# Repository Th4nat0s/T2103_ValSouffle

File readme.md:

Blow Gun controller for CNC
===========================

Print it on your CNC !

Push code to arduino
--------------------------------

### Arduino
Usb connection 
arduino framework 

Tips
----
`./serial` launch serial console through buspirate  
`pio run -t idedata` update libs, perpare env  
`pio run -t fuses` set the fuses  
`pio run -t upload -e release|debug` upload  a specific release version without serial debug  
`pio platform update --dry-run` check for updates

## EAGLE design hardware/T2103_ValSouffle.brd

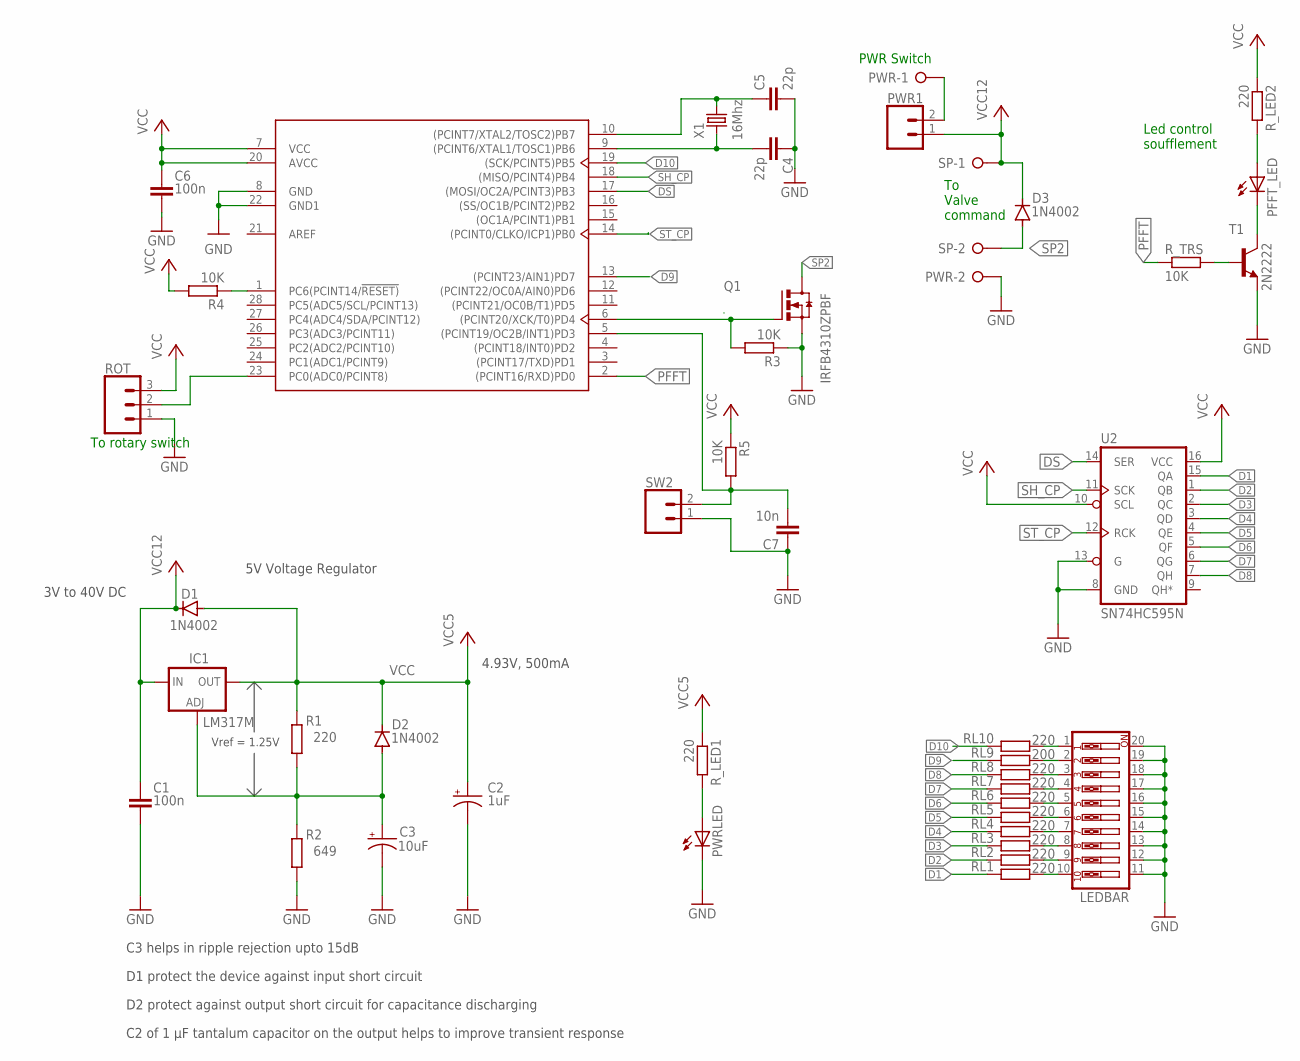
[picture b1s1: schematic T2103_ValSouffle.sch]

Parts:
C1, C6: 100n; C050-030X075
C2: 1uF; E1,8-4
C3: 10uF; E1,8-4
C4, C5: 22p; C025-025X050
C7: 10n; C025-025X050
D1, D2, D3: 1N4002; DO41-10
IC1: LM317MB; TO220L1; PARTNUMBER LM317M
LEDBAR: SW_DIP-10; EDG-10
PFFT_LED: LED5MM
PWR: W237-02P; W237-132
PWR1: CONN_02; 1X02
PWRLED: LED5MM
Q1: IRFB4310ZPBF; TO-220
R1: 220; 0207/10
R2: 649; 0207/10
R3, R4, R5: 10K; 0207/10
RL1, RL2, RL3, RL4, RL5, RL6, RL7, RL8, RL10: 220; 0207/10
RL9: 200; 0207/10
ROT: CONN_03; 1X03
R_LED1, R_LED2: 220; 0207/10
R_TRS: 10K; 0207/10
SP: W237-02P; W237-132
SW2: CONN_02; 1X02
T1: 2N2222; TO92-EBC-OVAL
U1: ATMEGA328P-PU; DIP-28
U2: SN74HC595N; DIP16
X1: 16Mhz; XTAL_HC49

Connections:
D1: RL1.2, U2.15 (QA)
D2: RL2.2, U2.1 (QB)
D3: RL3.2, U2.2 (QC)
D4: RL4.2, U2.3 (QD)
D5: RL5.2, U2.4 (QE)
D6: RL6.2, U2.5 (QF)
D7: RL7.2, U2.6 (QG)
D8: RL8.2, U2.7 (QH)
D9: RL9.2, U1.13 ((PCINT23/AIN1)PD7)
D10: RL10.2, U1.19 ((SCK/PCINT5)PB5)
DS: U1.17 ((MOSI/OC2A/PCINT3)PB3), U2.14 (SER)
GND: C1.2, C2.-, C3.-, C4.1, C5.2, C6.2, C7.1, LEDBAR.11, LEDBAR.12, LEDBAR.13, LEDBAR.14, LEDBAR.15, LEDBAR.16, LEDBAR.17, LEDBAR.18, LEDBAR.19, LEDBAR.20, PWR.2, PWRLED.K (C), Q1.S, R2.1, R3.1, ROT.1, SW2.1, T1.E, U1.8 (GND), U1.22 (GND1), U2.8 (GND), U2.13 (G)
unnamed: C3.+, D2.A, IC1.1 (ADJ), R1.1, R2.2
unnamed: C4.2, U1.9 ((PCINT6/XTAL1/TOSC1)PB6), X1.1
unnamed: C5.1, U1.10 ((PCINT7/XTAL2/TOSC2)PB7), X1.2
unnamed: Q1.G, R3.2, U1.6 ((PCINT20/XCK/T0)PD4)
unnamed: R4.1, U1.1 (PC6(PCINT14/!RESET))
unnamed: LEDBAR.1, RL10.1
unnamed: LEDBAR.2, RL9.1
unnamed: LEDBAR.3, RL8.1
unnamed: LEDBAR.4, RL7.1
unnamed: LEDBAR.5, RL6.1
unnamed: LEDBAR.6, RL5.1
unnamed: LEDBAR.7, RL4.1
unnamed: LEDBAR.8, RL3.1
unnamed: LEDBAR.9, RL2.1
unnamed: LEDBAR.10, RL1.1
unnamed: ROT.2, U1.23 (PC0(ADC0/PCINT8))
unnamed: PFFT_LED.A, R_LED2.2
unnamed: PFFT_LED.K (C), T1.C
unnamed: PWRLED.A, R_LED1.2
unnamed: R_TRS.2, T1.B
unnamed: C7.2, R5.2, SW2.2, U1.5 ((PCINT19/OC2B/INT1)PD3)
PFFT: R_TRS.1, U1.2 ((PCINT16/RXD)PD0)
SH_CP: U1.18 ((MISO/PCINT4)PB4), U2.11 (SCK)
SP2: D3.A, Q1.D, SP.2
ST_CP: U1.14 ((PCINT0/CLKO/ICP1)PB0), U2.12 (RCK)
VCC: C2.+, C6.1, D1.A, D2.C, IC1.2 (OUT), R1.2, R4.2, R5.1, ROT.3, R_LED1.1, R_LED2.1, U1.7 (VCC), U1.20 (AVCC), U2.10 (SCL), U2.16 (VCC)
VCC12: C1.1, D1.C, D3.C, IC1.3 (IN), PWR1.1, SP.1
VCCSHUT: PWR.1, PWR1.2

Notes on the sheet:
5V Voltage Regulator
C3 helps in ripple rejection upto 15dB
D1 protect the device against input short circuit
D2 protect against output short circuit for capacitance discharging
C2 of 1 µF tantalum capacitor on the output helps to improve transient response
4.93V, 500mA
3V to 40V DC
Vref = 1.25V
Led control soufflement
PWR Switch
To Valve command
To rotary switch

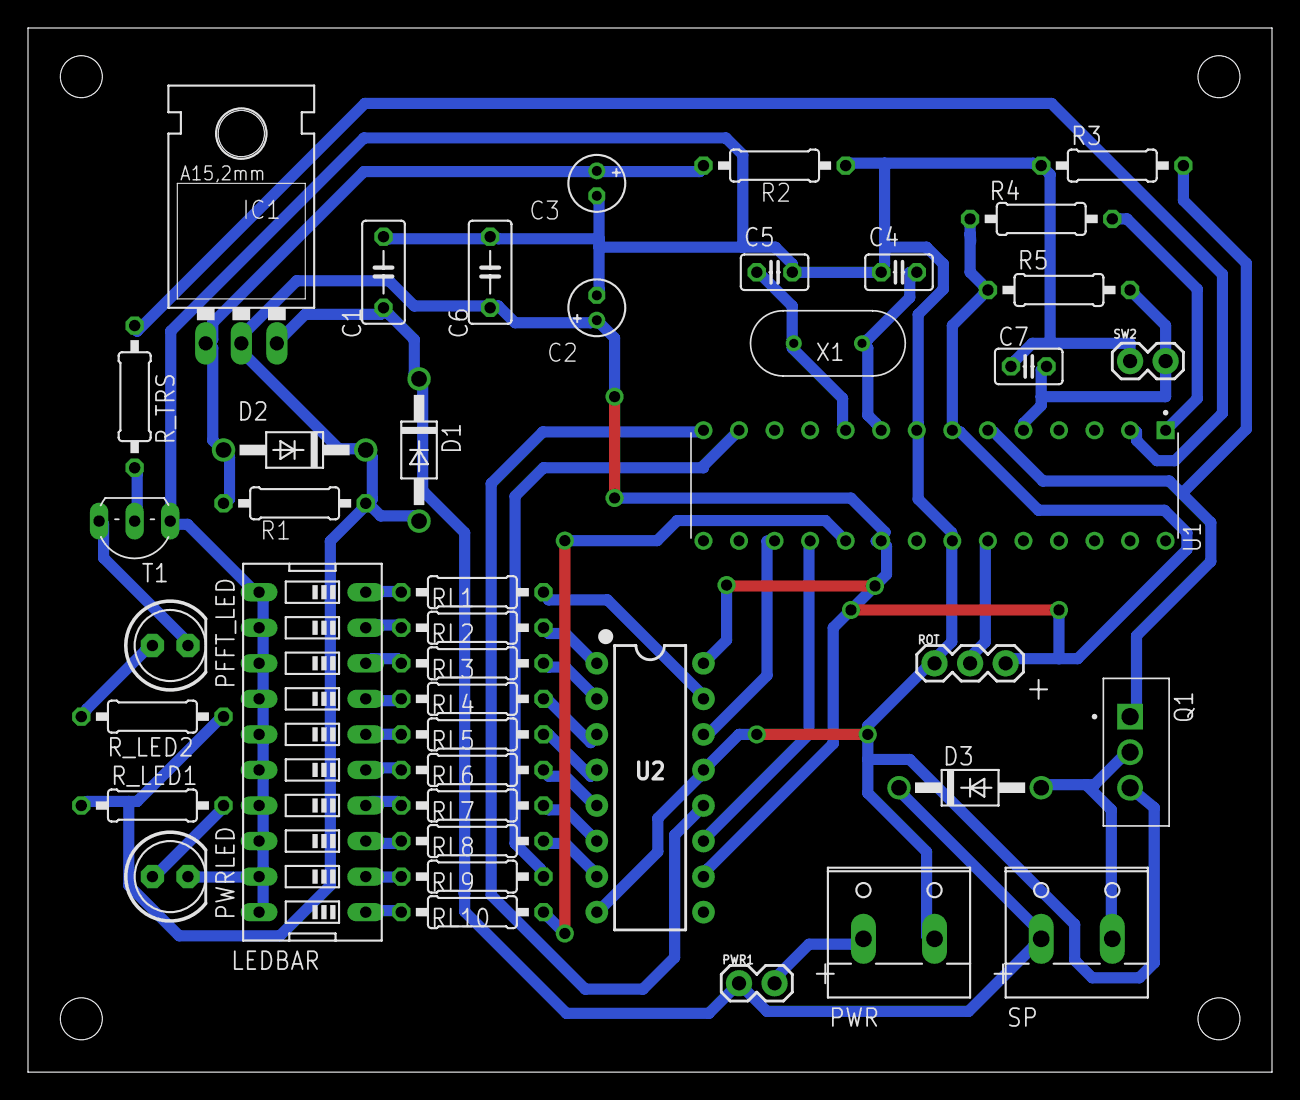
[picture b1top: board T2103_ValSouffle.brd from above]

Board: 2 copper layers, 88.9 x 74.6 mm, 42 parts (0 on the bottom side), 40 nets.

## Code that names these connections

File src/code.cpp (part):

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                  ATMEL Atmega328p / (ARDUINO Uno)

                             +-\/-+
            RST        PC6  1|    |28  PC5  (A5)    SCL
            Rx  (D0 )  PD0  2|    |27  PC4  (A4)    SDA
            Tx  (D1 )  PD1  3|    |26  PC3  (A3)
                (D2 )  PD2  4|    |25  PC2  (A2)
    PWM T2      (D3~)  PD3  5|    |24  PC1  (A1)
                (D4 )  PD4  6|    |23  PC0  (A0)
                       VCC  7|    |22  GND
                       GND  8|    |21  AREF
         Xtal1  (   )  PB6  9|    |20  AVCC
         Xtal2  (   )  PB7 10|    |19  PB5  (D13 )  SCK
        PWM T0  (D5~)  PD5 11|    |18  PB4  (D12 )  MISO
        PWM T0  (D6~)  PD6 12|    |17  PB3  (D11~)  MOSI PWM T2
                (D7 )  PD7 13|    |16  PB2  (D10~)       PWM T1
                (D8 )  PB0 14|    |15  PB1  (D 9~)       PWM T1
                             +----+

                 20 mA per pin / 200 mA overall
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*/

// Connections to the  74HC595 ( 8 Bit led driver )
const int latchPin = 8;  // PB0 connected to ST_CP
const int clockPin = 12;   // PB4 connected to SH_CP
const int dataPin = 11;   // PB3 connected to DS

// Connections to the leds
const int ledh1 = 7;   //  PD7 connected to Bit 9 - Led
const int ledh2 = 13;   //  PB5 connected to Bit 10 - Led
const int pfft = 0;  // PD0 connection to pffft led.

// Input pins
const int potPin = 0;     // PC2 selector, input pin for the potentiometer
const int ButtonPin = 3;  // PD3, manual blower button

// Output pins
const int t_pfft = 4;  // PD4 connection to the blower driver.

// Variables will change:
int but_pushed;
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  pinMode(latchPin, OUTPUT);
  pinMode(ledh1, OUTPUT); // Led 9
  pinMode(ledh2, OUTPUT);  // Led 10
  pinMode(pfft, OUTPUT);   // Led showing blow
  pinMode(t_pfft, OUTPUT);  // Transistor output for Blowing
  pinMode(ButtonPin, INPUT);  // Input button
  digitalWrite(pfft, 1);  // Active le pfft.
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
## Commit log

2021-03-24 1st push arduinoide code
2021-04-03 finalize routing
2021-04-05 Add manual switch
2021-04-05 add pdf
2021-04-07 update slide led code
2021-04-07 finalise motor control
2021-04-07 pimp my code
2021-05-18 test on device printed
2021-05-18 Hardware update
2021-05-19 update graph
2022-01-06 add datasheets

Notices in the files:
src/code.cpp:
Copyleft Thanat0s Since march 2021
parts and their libraries:
SparkFun-IC-Logic: Licensing: Creative Commons ShareAlike 4.0 International - https://creativecommons.org/licenses/by-sa/4.0
